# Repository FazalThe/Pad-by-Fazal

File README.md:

Pad by Fazal (XIAO RP2040)
---

This is a custom 9-key macro pad with a rotary encoder.

It is built using the Seeed Studio XIAO RP2040 and runs the KMK (CircuitPython) firmware.

🛠️ Hardware Overview
---

Microcontroller: Seeed Studio XIAO RP2040 (XIAO-RP2040-DIP)

Key Switches: 9 Mechanical Keys (3 columns x 3 rows) (SW_Cherry_MX_1.00u_PCB)

Rotary Encoder: 1 (Standard 2-pin data, without the push-button function) (RotaryEncoder_Alps_EC11E)

BOM
---
- 9x Cherry MX Switches

- 1× EC11-E Rotary Encoder (with push-button switch)

- 1x XIAO RP2040

- 9x Blank DSA Keycaps

- 4x M3x16 Bolt

- 4x M3 Heatset

| Schematic | PCB | Case|
|----------|----------|----------|
|     |      |      |

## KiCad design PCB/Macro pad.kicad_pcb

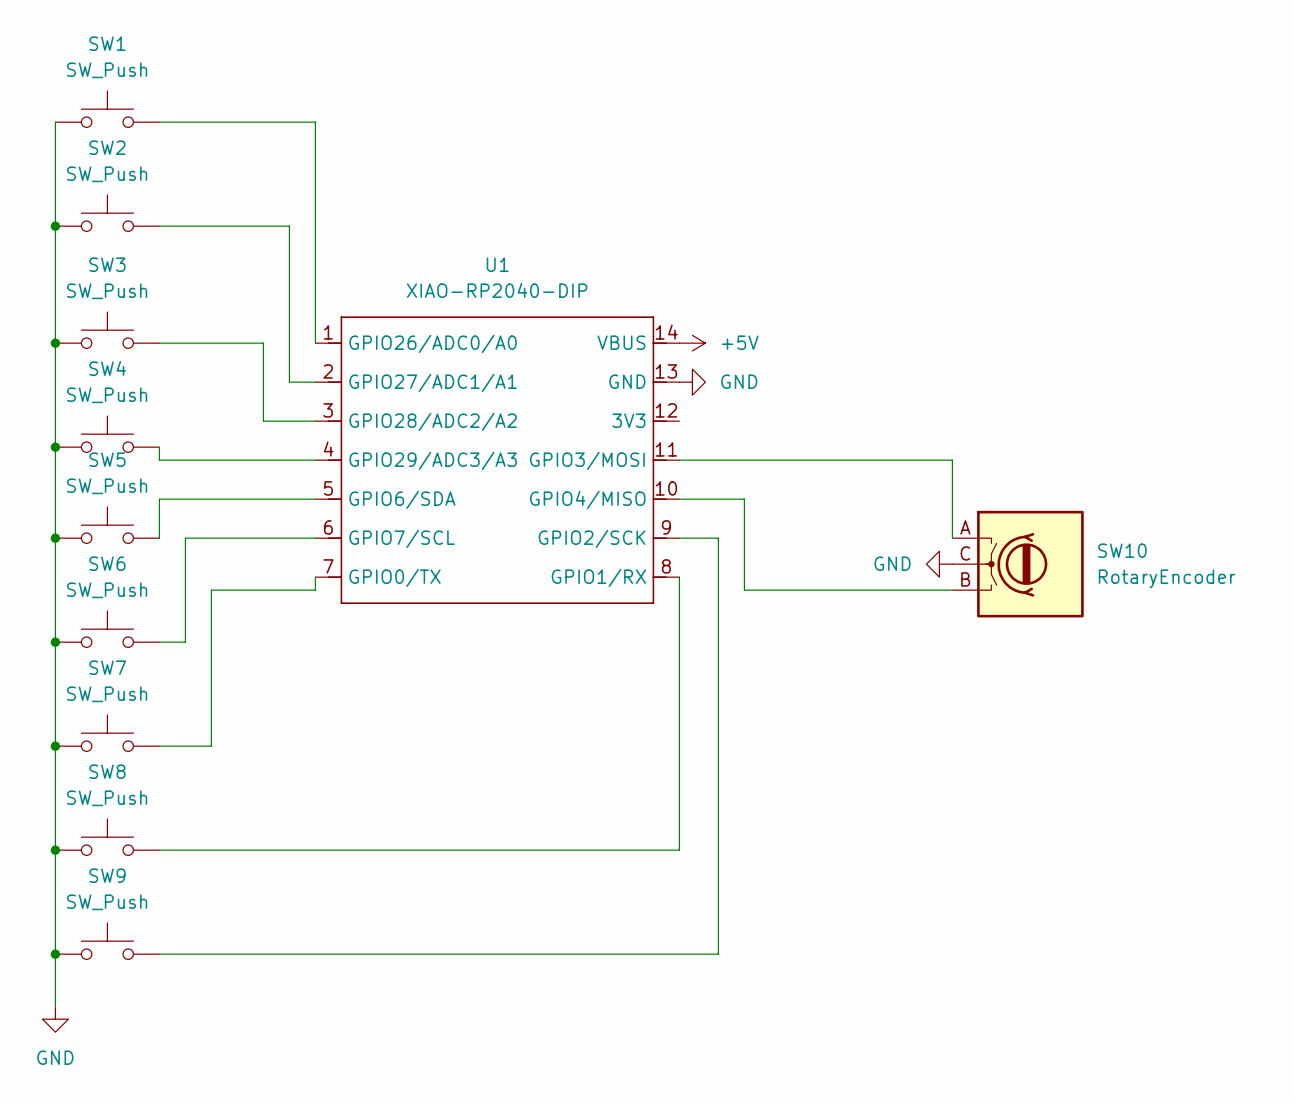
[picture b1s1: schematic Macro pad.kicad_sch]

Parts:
SW1, SW2, SW3, SW4, SW5, SW6, SW7, SW8, SW9: SW_Push; SW_Cherry_MX_1.00u_PCB
SW10: RotaryEncoder; RotaryEncoder_Alps_EC11E-Switch_Vertical_H20mm
U1: XIAO-RP2040-DIP

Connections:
+5V: U1.14 (VBUS)
GND: SW1.1, SW2.1, SW3.1, SW4.1, SW5.1, SW6.1, SW7.1, SW8.1, SW9.1, SW10.C, U1.13 (GND)
unnamed: SW7.2, U1.7 (GPIO0/TX)
unnamed: SW8.2, U1.8 (GPIO1/RX)
unnamed: SW9.2, U1.9 (GPIO2/SCK)
unnamed: SW10.A, U1.11 (GPIO3/MOSI)
unnamed: SW10.B, U1.10 (GPIO4/MISO)
unnamed: SW5.2, U1.5 (GPIO6/SDA)
unnamed: SW6.2, U1.6 (GPIO7/SCL)
unnamed: SW1.2, U1.1 (GPIO26/ADC0/A0)
unnamed: SW2.2, U1.2 (GPIO27/ADC1/A1)
unnamed: SW3.2, U1.3 (GPIO28/ADC2/A2)
unnamed: SW4.2, U1.4 (GPIO29/ADC3/A3)

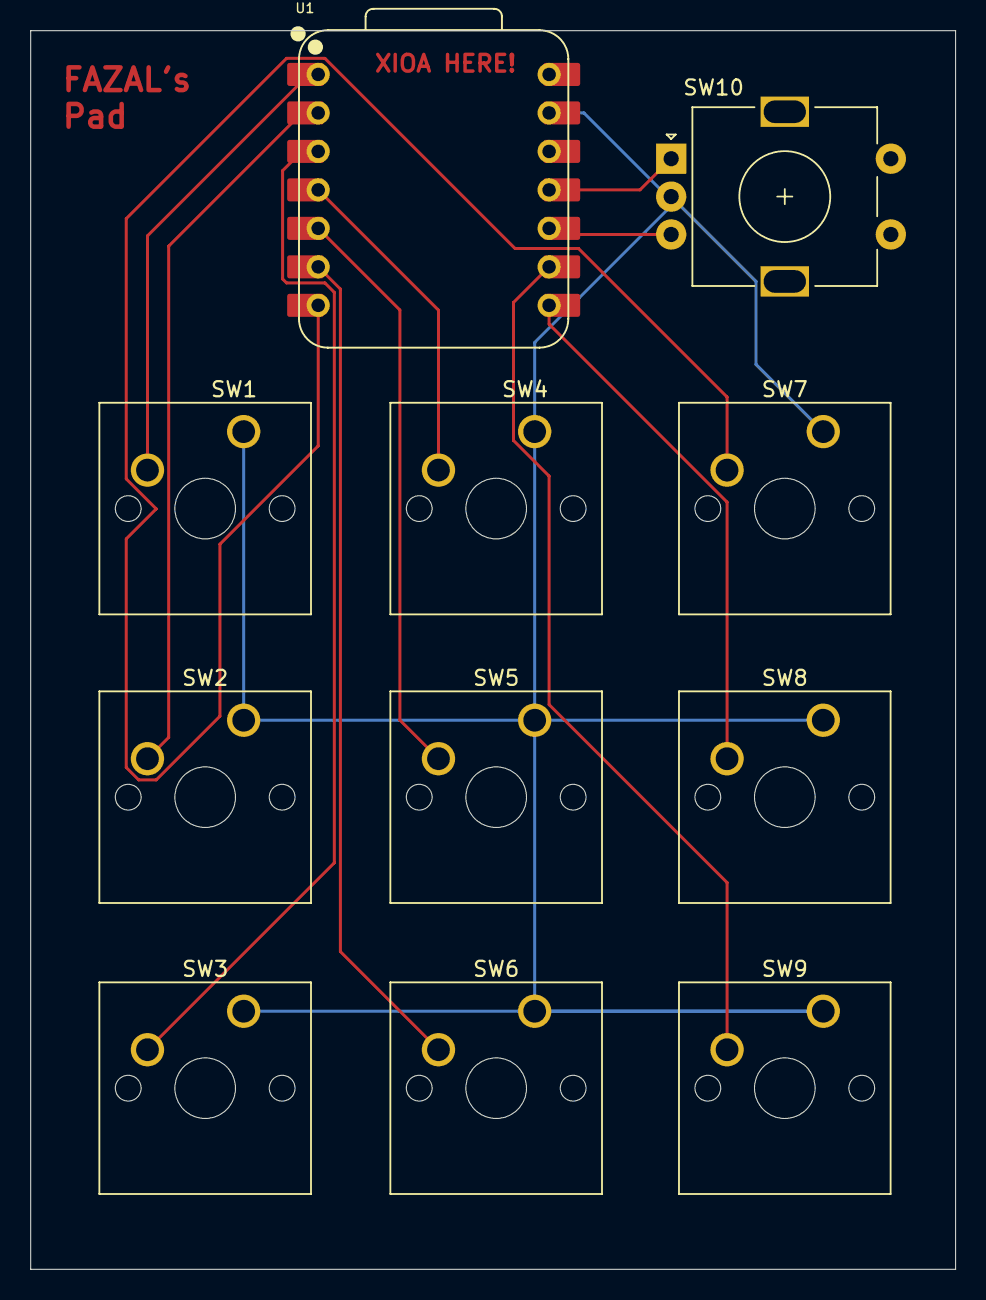
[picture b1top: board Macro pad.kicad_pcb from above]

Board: 2 copper layers, 61.1 x 81.8 mm, 11 parts (0 on the bottom side), 12 nets.

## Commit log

2025-12-04 Initialize README with project details
    Added project description and hardware overview.
2025-12-05 Enhance README with images and BOM
    Added images and BOM details to the README.
